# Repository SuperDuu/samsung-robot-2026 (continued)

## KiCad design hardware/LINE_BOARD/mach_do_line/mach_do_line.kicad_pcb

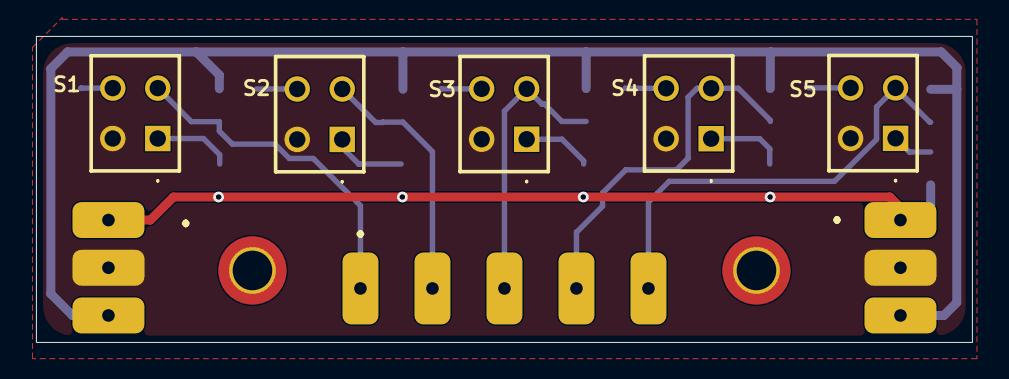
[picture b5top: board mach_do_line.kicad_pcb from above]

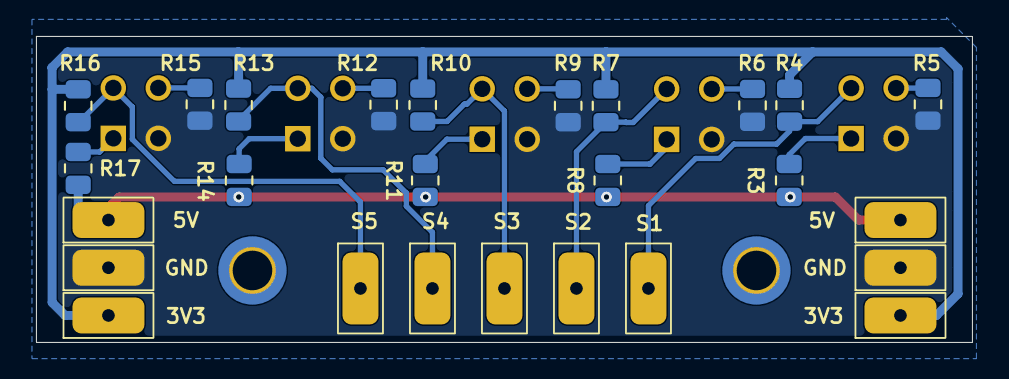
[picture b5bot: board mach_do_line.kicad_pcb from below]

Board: 2 copper layers, 52.0 x 17.0 mm, 33 parts (26 on the bottom side), 18 nets.

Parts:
3V3, 3V3#2, 5V, 5V#2: Conn_01x01_Pin; PAD-2x4mm-SMD
GND: Conn_01x01_Pin; PAD-2x4mm-SMD
GND#2: Conn_01x01_Pin; PAD-2x4mm-SMD
H1, H2: MountingHole; MountingHole_2.2mm_M2_ISO14580_Pad_TopBottom
J2, J10, J11, J12, J18: Conn_01x01_Pin; PAD-2x4mm-SMD
R3, R8, R11, R14, R17: 220R; R_0805_2012Metric
R4, R7, R10, R13, R16: 10K; R_0805_2012Metric
R5, R6, R9, R12, R15: 100R; R_0805_2012Metric
S1, S2, S3, S4, S5: RPR-220; RPR220

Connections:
+3V3: 3V3.1 (Pin_1_1), 3V3#2.1 (Pin_1_1), R4.2, R7.2, R10.2, R13.2, R16.2
+5V: 5V.1 (Pin_1_1), 5V#2.1 (Pin_1_1), R3.1, R8.1, R11.1, R14.1, R17.1
/s1: J2.1 (Pin_1_1), R4.1, S1.4 (C)
/s2: J10.1 (Pin_1_1), R7.1, S2.4 (C)
/s3: J11.1 (Pin_1_1), R10.1, S3.4 (C)
/s4: J12.1 (Pin_1_1), R13.1, S4.4 (C)
/s5: J18.1 (Pin_1_1), R16.1, S5.4 (C)
GND: GND.1 (Pin_1_1), GND#2.1 (Pin_1_1), R5.2, R6.2, R9.2, R12.2, R15.2, S1.2 (K), S2.2 (K), S3.2 (K), S4.2 (K), S5.2 (K)
unnamed: R3.2, S1.1 (A)
unnamed: R5.1, S1.3 (E)
unnamed: R8.2, S2.1 (A)
unnamed: R6.1, S2.3 (E)
unnamed: R11.2, S3.1 (A)
unnamed: R9.1, S3.3 (E)
unnamed: R14.2, S4.1 (A)
unnamed: R12.1, S4.3 (E)
unnamed: R17.2, S5.1 (A)
unnamed: R15.1, S5.3 (E)

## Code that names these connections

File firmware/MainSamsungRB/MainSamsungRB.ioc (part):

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Mcu.Name=STM32F405RGTx
Mcu.Package=LQFP64
Mcu.UserName=STM32F405RGTx
PA0-WKUP.Signal=ADCx_IN0
PA1.GPIOParameters=GPIO_Speed,PinState,GPIO_PuPd,GPIO_Label
PA1.GPIO_Label=RE_DE
PA1.GPIO_PuPd=GPIO_NOPULL
PA1.GPIO_Speed=GPIO_SPEED_FREQ_HIGH
PA1.PinState=GPIO_PIN_RESET
PA1.Signal=GPIO_Output
PA10.Mode=Asynchronous
PA10.Signal=USART1_RX
PA11.Mode=Device_Only
PA11.Signal=USB_OTG_FS_DM
PA12.Mode=Device_Only
PA12.Signal=USB_OTG_FS_DP
PA13.Mode=Serial_Wire
PA13.Signal=SYS_JTMS-SWDIO
PA14.Mode=Serial_Wire
PA14.Signal=SYS_JTCK-SWCLK
PA15.GPIOParameters=GPIO_Label
PA15.GPIO_Label=SW2
PA15.Signal=GPIO_Input
PA2.Mode=Asynchronous
PA2.Signal=USART2_TX
PA3.Mode=Asynchronous
PA3.Signal=USART2_RX
PA4.GPIOParameters=GPIO_Speed,PinState,GPIO_Label
PA4.GPIO_Label=MH_CS
PA4.GPIO_Speed=GPIO_SPEED_FREQ_HIGH
PA4.PinState=GPIO_PIN_SET
PA4.Signal=GPIO_Output
PA5.Mode=TX_Only_Simplex_Unidirect_Master
PA5.Signal=SPI1_SCK
PA7.Mode=TX_Only_Simplex_Unidirect_Master
PA7.Signal=SPI1_MOSI
PA8.Mode=I2C
PA8.Signal=I2C3_SCL
PA9.Mode=Asynchronous
PA9.Signal=USART1_TX
PB0.Signal=S_TIM3_CH3
PB1.Signal=S_TIM3_CH4
PB10.Mode=I2C
PB10.Signal=I2C2_SCL
PB11.Mode=I2C
PB11.Signal=I2C2_SDA
PB12.GPIOParameters=GPIO_Label
PB12.GPIO_Label=SW1
PB12.Signal=GPIO_Input
PB13.GPIOParameters=PinState,GPIO_Label
PB13.GPIO_Label=LS4
PB13.PinState=GPIO_PIN_RESET
PB13.Signal=GPIO_Output
PB14.Signal=S_TIM12_CH1
PB15.Signal=S_TIM12_CH2
PB2.GPIOParameters=PinState,GPIO_Label
PB2.GPIO_Label=L11
PB2.PinState=GPIO_PIN_SET
PB2.Signal=GPIO_Output
PB3.GPIOParameters=PinState,GPIO_Label
PB3.GPIO_Label=L8
PB3.PinState=GPIO_PIN_SET
PB3.Signal=GPIO_Output
PB4.GPIOParameters=PinState,GPIO_Label
PB4.GPIO_Label=L7
PB4.PinState=GPIO_PIN_SET
PB4.Signal=GPIO_Output
PB5.GPIOParameters=PinState,GPIO_Label
PB5.GPIO_Label=L6
PB5.PinState=GPIO_PIN_SET
PB5.Signal=GPIO_Output
PB6.GPIOParameters=PinState,GPIO_Label
PB6.GPIO_Label=L5
PB6.PinState=GPIO_PIN_SET
PB6.Signal=GPIO_Output
PB7.GPIOParameters=PinState,GPIO_Label
PB7.GPIO_Label=L4
PB7.PinState=GPIO_PIN_SET
PB7.Signal=GPIO_Output
PB8.Signal=S_TIM4_CH3
PB9.Signal=S_TIM4_CH4
PC0.GPIOParameters=GPIO_Speed,PinState,GPIO_Label
PC0.GPIO_Label=s3
PC0.GPIO_Speed=GPIO_SPEED_FREQ_VERY_HIGH
PC0.PinState=GPIO_PIN_RESET
PC0.Signal=GPIO_Output
PC1.GPIOParameters=GPIO_Speed,PinState,GPIO_Label
PC1.GPIO_Label=s2
PC1.GPIO_Speed=GPIO_SPEED_FREQ_VERY_HIGH
PC1.PinState=GPIO_PIN_RESET
PC1.Signal=GPIO_Output
PC10.Mode=Asynchronous
PC10.Signal=UART4_TX
PC11.Mode=Asynchronous
PC11.Signal=UART4_RX
PC12.GPIOParameters=PinState,GPIO_Label
PC12.GPIO_Label=L10
PC12.PinState=GPIO_PIN_SET
PC12.Signal=GPIO_Output
PC13-ANTI_TAMP.GPIOParameters=PinState,GPIO_Label
PC13-ANTI_TAMP.GPIO_Label=L3
PC13-ANTI_TAMP.PinState=GPIO_PIN_SET
PC13-ANTI_TAMP.Signal=GPIO_Output
PC14-OSC32_IN.GPIOParameters=PinState,GPIO_Label
PC14-OSC32_IN.GPIO_Label=L2
PC14-OSC32_IN.PinState=GPIO_PIN_SET
PC14-OSC32_IN.Signal=GPIO_Output
PC15-OSC32_OUT.GPIOParameters=PinState,GPIO_Label
PC15-OSC32_OUT.GPIO_Label=L1
PC15-OSC32_OUT.PinState=GPIO_PIN_SET
PC15-OSC32_OUT.Signal=GPIO_Output
PC2.GPIOParameters=GPIO_Speed,PinState,GPIO_Label
PC2.GPIO_Label=s1
PC2.GPIO_Speed=GPIO_SPEED_FREQ_VERY_HIGH
PC2.PinState=GPIO_PIN_RESET
PC2.Signal=GPIO_Output
PC3.GPIOParameters=GPIO_Speed,PinState,GPIO_Label
PC3.GPIO_Label=s0
PC3.GPIO_Speed=GPIO_SPEED_FREQ_VERY_HIGH
PC3.PinState=GPIO_PIN_RESET
PC3.Signal=GPIO_Output
PC4.GPIOParameters=GPIO_Speed,PinState,GPIO_Label
PC4.GPIO_Label=MH_RST
PC4.GPIO_Speed=GPIO_SPEED_FREQ_LOW
PC4.PinState=GPIO_PIN_SET
PC4.Signal=GPIO_Output
PC5.GPIOParameters=GPIO_Speed,PinState,GPIO_Label
PC5.GPIO_Label=MH_DC
PC5.GPIO_Speed=GPIO_SPEED_FREQ_HIGH
PC5.PinState=GPIO_PIN_RESET
PC5.Signal=GPIO_Output
PC6.GPIOParameters=PinState,GPIO_Label
PC6.GPIO_Label=LS3
PC6.PinState=GPIO_PIN_RESET
PC6.Signal=GPIO_Output
PC7.GPIOParameters=PinState,GPIO_Label
PC7.GPIO_Label=LS2
PC7.PinState=GPIO_PIN_RESET
PC7.Signal=GPIO_Output
PC8.GPIOParameters=PinState,GPIO_Label
PC8.GPIO_Label=LS1
PC8.PinState=GPIO_PIN_RESET
PC8.Signal=GPIO_Output
PC9.Mode=I2C
PC9.Signal=I2C3_SDA
PD2.GPIOParameters=PinState,GPIO_Label
PD2.GPIO_Label=L9
PD2.PinState=GPIO_PIN_SET
PD2.Signal=GPIO_Output
PH0-OSC_IN.Mode=HSE-External-Oscillator
PH0-OSC_IN.Signal=RCC_OSC_IN
PH1-OSC_OUT.Mode=HSE-External-Oscillator
PH1-OSC_OUT.Signal=RCC_OSC_OUT
RCC.HSE_VALUE=8000000
RCC.SYSCLKFreq_VALUE=168000000
RCC.SYSCLKSource=RCC_SYSCLKSOURCE_PLLCLK
board=custom

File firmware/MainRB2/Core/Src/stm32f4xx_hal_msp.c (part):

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
    __HAL_RCC_GPIOA_CLK_ENABLE();
    /**ADC1 GPIO Configuration
    PA0-WKUP     ------> ADC1_IN0
    */
    GPIO_InitStruct.Pin = GPIO_PIN_0;
    GPIO_InitStruct.Mode = GPIO_MODE_ANALOG;
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    __HAL_RCC_ADC1_CLK_DISABLE();

    /**ADC1 GPIO Configuration
    PA0-WKUP     ------> ADC1_IN0
    */
    HAL_GPIO_DeInit(GPIOA, GPIO_PIN_0);

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
    __HAL_RCC_GPIOB_CLK_ENABLE();
    /**I2C2 GPIO Configuration
    PB10     ------> I2C2_SCL
    PB11     ------> I2C2_SDA
    */
    GPIO_InitStruct.Pin = GPIO_PIN_10|GPIO_PIN_11;
    GPIO_InitStruct.Mode = GPIO_MODE_AF_OD;
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    __HAL_RCC_GPIOC_CLK_ENABLE();
    __HAL_RCC_GPIOA_CLK_ENABLE();
    /**I2C3 GPIO Configuration
    PC9     ------> I2C3_SDA
    PA8     ------> I2C3_SCL
    */
    GPIO_InitStruct.Pin = GPIO_PIN_9;
    GPIO_InitStruct.Mode = GPIO_MODE_AF_OD;
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    __HAL_RCC_I2C2_CLK_DISABLE();

    /**I2C2 GPIO Configuration
    PB10     ------> I2C2_SCL
    PB11     ------> I2C2_SDA
    */
    HAL_GPIO_DeInit(GPIOB, GPIO_PIN_10);

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    __HAL_RCC_I2C3_CLK_DISABLE();

    /**I2C3 GPIO Configuration
    PC9     ------> I2C3_SDA
    PA8     ------> I2C3_SCL
    */
    HAL_GPIO_DeInit(GPIOC, GPIO_PIN_9);

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
    __HAL_RCC_GPIOA_CLK_ENABLE();
    /**SPI1 GPIO Configuration
    PA5     ------> SPI1_SCK
    PA7     ------> SPI1_MOSI
    */
    GPIO_InitStruct.Pin = GPIO_PIN_5|GPIO_PIN_7;
    GPIO_InitStruct.Mode = GPIO_MODE_AF_PP;
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    __HAL_RCC_SPI1_CLK_DISABLE();

    /**SPI1 GPIO Configuration
    PA5     ------> SPI1_SCK
    PA7     ------> SPI1_MOSI
    */
    HAL_GPIO_DeInit(GPIOA, GPIO_PIN_5|GPIO_PIN_7);

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    /* USER CODE END TIM4_MspPostInit 0 */
    __HAL_RCC_GPIOB_CLK_ENABLE();
    /**TIM4 GPIO Configuration
    PB8     ------> TIM4_CH3
    */
    GPIO_InitStruct.Pin = GPIO_PIN_8;
    GPIO_InitStruct.Mode = GPIO_MODE_AF_PP;
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
    __HAL_RCC_GPIOB_CLK_ENABLE();
    /**TIM12 GPIO Configuration
    PB15     ------> TIM12_CH2
    */
    GPIO_InitStruct.Pin = GPIO_PIN_15;
    GPIO_InitStruct.Mode = GPIO_MODE_AF_PP;
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
    __HAL_RCC_GPIOC_CLK_ENABLE();
    /**UART4 GPIO Configuration
    PC10     ------> UART4_TX
    PC11     ------> UART4_RX
    */
    GPIO_InitStruct.Pin = GPIO_PIN_10|GPIO_PIN_11;
    GPIO_InitStruct.Mode = GPIO_MODE_AF_PP;
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
    __HAL_RCC_GPIOA_CLK_ENABLE();
    /**USART1 GPIO Configuration
    PA9     ------> USART1_TX
    PA10     ------> USART1_RX
    */
    GPIO_InitStruct.Pin = GPIO_PIN_9|GPIO_PIN_10;
    GPIO_InitStruct.Mode = GPIO_MODE_AF_PP;
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
    __HAL_RCC_GPIOA_CLK_ENABLE();
    /**USART2 GPIO Configuration
    PA2     ------> USART2_TX
    PA3     ------> USART2_RX
    */
    GPIO_InitStruct.Pin = GPIO_PIN_2|GPIO_PIN_3;
    GPIO_InitStruct.Mode = GPIO_MODE_AF_PP;
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    __HAL_RCC_UART4_CLK_DISABLE();

    /**UART4 GPIO Configuration
    PC10     ------> UART4_TX
    PC11     ------> UART4_RX
    */
    HAL_GPIO_DeInit(GPIOC, GPIO_PIN_10|GPIO_PIN_11);

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    __HAL_RCC_USART1_CLK_DISABLE();

    /**USART1 GPIO Configuration
    PA9     ------> USART1_TX
    PA10     ------> USART1_RX
    */
    HAL_GPIO_DeInit(GPIOA, GPIO_PIN_9|GPIO_PIN_10);

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    __HAL_RCC_USART2_CLK_DISABLE();

    /**USART2 GPIO Configuration
    PA2     ------> USART2_TX
    PA3     ------> USART2_RX
    */
    HAL_GPIO_DeInit(GPIOA, GPIO_PIN_2|GPIO_PIN_3);

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
    __HAL_RCC_GPIOA_CLK_ENABLE();
    /**USB_OTG_FS GPIO Configuration
    PA11     ------> USB_OTG_FS_DM
    PA12     ------> USB_OTG_FS_DP
    */
    GPIO_InitStruct.Pin = GPIO_PIN_11|GPIO_PIN_12;
    GPIO_InitStruct.Mode = GPIO_MODE_AF_PP;
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    __HAL_RCC_USB_OTG_FS_CLK_DISABLE();

    /**USB_OTG_FS GPIO Configuration
    PA11     ------> USB_OTG_FS_DM
    PA12     ------> USB_OTG_FS_DP
    */
    HAL_GPIO_DeInit(GPIOA, GPIO_PIN_11|GPIO_PIN_12);

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
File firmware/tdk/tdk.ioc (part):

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Mcu.Name=STM32G030F6Px
Mcu.Package=TSSOP20
Mcu.UserName=STM32G030F6Px
PA1.GPIOParameters=GPIO_Speed,PinState,GPIO_PuPd,GPIO_Label
PA1.GPIO_Label=CLK_PS2
PA1.GPIO_PuPd=GPIO_NOPULL
PA1.GPIO_Speed=GPIO_SPEED_FREQ_HIGH
PA1.PinState=GPIO_PIN_SET
PA1.Signal=GPIO_Output
PA11\ [PA9].GPIOParameters=PinState,GPIO_Label
PA11\ [PA9].GPIO_Label=BUZZER
PA11\ [PA9].PinState=GPIO_PIN_RESET
PA11\ [PA9].Signal=GPIO_Output
PA12\ [PA10].GPIOParameters=PinState,GPIO_Label
PA12\ [PA10].GPIO_Label=LED_1
PA12\ [PA10].PinState=GPIO_PIN_RESET
PA12\ [PA10].Signal=GPIO_Output
PA13.Mode=Serial_Wire
PA13.Signal=SYS_SWDIO
PA14-BOOT0.Mode=Serial_Wire
PA14-BOOT0.Signal=SYS_SWCLK
PA14-BOOT0__PA15.StandardMode=true
PA2.Mode=Asynchronous
PA2.Signal=USART2_TX
PA3.Mode=Asynchronous
PA3.Signal=USART2_RX
PA4.GPIOParameters=GPIO_Speed,PinState,GPIO_PuPd,GPIO_Label
PA4.GPIO_Label=CS_PS2
PA4.GPIO_PuPd=GPIO_NOPULL
PA4.GPIO_Speed=GPIO_SPEED_FREQ_HIGH
PA4.PinState=GPIO_PIN_SET
PA4.Signal=GPIO_Output
PA6.GPIOParameters=PinState,GPIO_Label
PA6.GPIO_Label=LED_3
PA6.PinState=GPIO_PIN_RESET
PA6.Signal=GPIO_Output
PA8.GPIOParameters=GPIO_PuPd,GPIO_Label
PA8.GPIO_Label=SW
PA8.GPIO_PuPd=GPIO_NOPULL
PA8.Signal=GPIO_Input
PB0__PB1__PB2__PA8.StandardMode=true
PB3.GPIOParameters=GPIO_PuPd,GPIO_Label
PB3.GPIO_Label=BUTTON
PB3.GPIO_PuPd=GPIO_NOPULL
PB3.Signal=GPIO_Input
PB3__PB4__PB5__PB6.StandardMode=true
PB7.GPIOParameters=GPIO_Speed,PinState,GPIO_PuPd,GPIO_Label
PB7.GPIO_Label=DO_PS2
PB7.GPIO_PuPd=GPIO_NOPULL
PB7.GPIO_Speed=GPIO_SPEED_FREQ_HIGH
PB7.PinState=GPIO_PIN_SET
PB7.Signal=GPIO_Output
PB7__PB8.StandardMode=true
PB9.GPIOParameters=PinState,GPIO_Label
PB9.GPIO_Label=LED_2
PB9.PinState=GPIO_PIN_RESET
PB9.Signal=GPIO_Output
PC14-OSC32_IN\ (PC14)__PB9.StandardMode=true
PC15-OSC32_OUT\ (PC15).GPIOParameters=GPIO_PuPd,GPIO_Label
PC15-OSC32_OUT\ (PC15).GPIO_Label=DI_PS2
PC15-OSC32_OUT\ (PC15).GPIO_PuPd=GPIO_PULLUP
PC15-OSC32_OUT\ (PC15).Signal=GPIO_Input
RCC.HSE_VALUE=8000000
RCC.SYSCLKFreq_VALUE=64000000
RCC.SYSCLKSource=RCC_SYSCLKSOURCE_PLLCLK
board=custom

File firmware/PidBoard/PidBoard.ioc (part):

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Mcu.Name=STM32G030F6Px
Mcu.Package=TSSOP20
Mcu.UserName=STM32G030F6Px
PA1.GPIOParameters=GPIO_Speed,PinState,GPIO_PuPd,GPIO_Label
PA1.GPIO_Label=RE_DE
PA1.GPIO_PuPd=GPIO_NOPULL
PA1.GPIO_Speed=GPIO_SPEED_FREQ_HIGH
PA1.PinState=GPIO_PIN_RESET
PA1.Signal=GPIO_Output
PA13.Mode=Serial_Wire
PA13.Signal=SYS_SWDIO
PA14-BOOT0.Mode=Serial_Wire
PA14-BOOT0.Signal=SYS_SWCLK
PA14-BOOT0__PA15.StandardMode=true
PA2.Mode=Asynchronous
PA2.Signal=USART2_TX
PA3.Mode=Asynchronous
PA3.Signal=USART2_RX
PA4.GPIOParameters=GPIO_Speed,PinState,GPIO_PuPd,GPIO_Label
PA4.GPIO_Label=S2
PA4.GPIO_PuPd=GPIO_NOPULL
PA4.GPIO_Speed=GPIO_SPEED_FREQ_LOW
PA4.PinState=GPIO_PIN_RESET
PA4.Signal=GPIO_Output
PA6.GPIOParameters=GPIO_PuPd,GPIO_Label
PA6.GPIO_Label=ENC_A
PA6.GPIO_PuPd=GPIO_PULLUP
PA6.Signal=S_TIM3_CH1
PA7.GPIOParameters=GPIO_PuPd,GPIO_Label
PA7.GPIO_Label=ENC_B
PA7.GPIO_PuPd=GPIO_PULLUP
PA7.Signal=S_TIM3_CH2
PA8.Signal=S_TIM1_CH1
PB0__PB1__PB2__PA8.StandardMode=true
PB3.Signal=S_TIM1_CH2
PB3__PB4__PB5__PB6.StandardMode=true
PB7.GPIOParameters=GPIO_Speed,PinState,GPIO_PuPd,GPIO_Label
PB7.GPIO_Label=S
PB7.GPIO_PuPd=GPIO_NOPULL
PB7.GPIO_Speed=GPIO_SPEED_FREQ_LOW
PB7.PinState=GPIO_PIN_RESET
PB7.Signal=GPIO_Output
PB7__PB8.StandardMode=true
PC14-OSC32_IN\ (PC14).GPIOParameters=GPIO_Speed,PinState,GPIO_PuPd,GPIO_Label
PC14-OSC32_IN\ (PC14).GPIO_Label=LED2
PC14-OSC32_IN\ (PC14).GPIO_PuPd=GPIO_NOPULL
PC14-OSC32_IN\ (PC14).GPIO_Speed=GPIO_SPEED_FREQ_LOW
PC14-OSC32_IN\ (PC14).PinState=GPIO_PIN_SET
PC14-OSC32_IN\ (PC14).Signal=GPIO_Output
PC14-OSC32_IN\ (PC14)__PB9.StandardMode=true
PC15-OSC32_OUT\ (PC15).GPIOParameters=GPIO_Speed,PinState,GPIO_PuPd,GPIO_Label
PC15-OSC32_OUT\ (PC15).GPIO_Label=LED1
PC15-OSC32_OUT\ (PC15).GPIO_PuPd=GPIO_NOPULL
PC15-OSC32_OUT\ (PC15).GPIO_Speed=GPIO_SPEED_FREQ_LOW
PC15-OSC32_OUT\ (PC15).PinState=GPIO_PIN_SET
PC15-OSC32_OUT\ (PC15).Signal=GPIO_Output
RCC.HSE_VALUE=8000000
RCC.SYSCLKFreq_VALUE=64000000
RCC.SYSCLKSource=RCC_SYSCLKSOURCE_PLLCLK
board=custom

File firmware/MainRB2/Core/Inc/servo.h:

/**
  ******************************************************************************
  * @file    servo.h
  * @brief   2-mode Servo driver (0-270 deg positional & 360 deg continuous speed)
  *          for the PWM outputs on MainRB2 (TIM3 CH3/4, TIM12 CH2, TIM4 CH3/4).
  *          Requires 50 Hz timer base: PSC = 83, ARR = 19999 -> 1 tick = 1 us.
  ******************************************************************************
  */

#ifndef INC_SERVO_H_
#define INC_SERVO_H_

#ifdef __cplusplus
extern "C" {
#endif

#ifdef UNIT_TEST_HOST
#include "mock_hal.h"
#else
#include "main.h"
#endif

#include <stdbool.h>
#include <stdint.h>

#define SERVO_PWM_MIN_US               500U
#define SERVO_PWM_NEUTRAL_US           1500U
#define SERVO_PWM_MAX_US               2500U
#define SERVO_180_MAX_DEG              180.0f
#define SERVO_270_MAX_DEG              270.0f
#define SERVO_CLAMP_DEFAULT_OPEN_DEG   15.0f
#define SERVO_CLAMP_DEFAULT_CLOSE_DEG  0.0f
#define SERVO_360_DEFAULT_HALF_SPAN_US 500U   /* 1000..2000 us continuous range (pass 1000 for 500..2500 us) */
#define SERVO_DEFAULT_DEADBAND_PCT     2.0f

typedef enum
{
  SERVO_CH_1 = 0U, /* PB0  - TIM3_CH3  (J2)  */
  SERVO_CH_2 = 1U, /* Reserved: PB1 (J34) is BAUMER_INPUT */
  SERVO_CH_3 = 2U, /* Unused: PB14 (J35) */
  SERVO_CH_4 = 3U, /* PB15 - TIM12_CH2 (J36) */
  SERVO_CH_5 = 4U, /* PB8  - TIM4_CH3  (J37) */
  SERVO_CH_6 = 5U, /* PB9  - TIM4_CH4  (J38) */
  SERVO_NUM_CHANNELS = 6U
} Servo_Channel_t;

typedef enum
{
  SERVO_MODE_UNCONFIGURED   = 0U,
  SERVO_MODE_ANGLE_270      = 1U,
  SERVO_MODE_CONTINUOUS_360 = 2U,
  SERVO_MODE_ANGLE_180      = 3U
} Servo_Mode_t;

typedef struct
{
  Servo_Mode_t mode;
  uint16_t     min_us;
  uint16_t     neutral_us;
  uint16_t     max_us;
  float        deadband_pct;
  bool         inverted;
  bool         started;
  uint16_t     current_us;
  float        last_cmd;
} Servo_ChannelState_t;

HAL_StatusTypeDef Servo_Init(TIM_HandleTypeDef *htim3,
                             TIM_HandleTypeDef *htim4,
                             TIM_HandleTypeDef *htim12);

HAL_StatusTypeDef Servo_Config270(Servo_Channel_t ch,
                                  uint16_t min_us,
                                  uint16_t max_us,
                                  bool inverted);

HAL_StatusTypeDef Servo_Config180(Servo_Channel_t ch,
                                  uint16_t min_us,
                                  uint16_t max_us,
                                  bool inverted);

HAL_StatusTypeDef Servo_Config360(Servo_Channel_t ch,
                                  uint16_t neutral_us,
                                  uint16_t half_span_us,
                                  float deadband_pct,
                                  bool inverted);

/* Mode 1: Positional 0.0 .. 270.0 degrees (linearly mapped to min_us..max_us) */
HAL_StatusTypeDef Servo_SetAngle270(Servo_Channel_t ch, float angle_deg);

/* Mode 3: Positional 0.0 .. 180.0 degrees (linearly mapped to min_us..max_us) */
HAL_StatusTypeDef Servo_SetAngle180(Servo_Channel_t ch, float angle_deg);

/* Mode 2: Continuous 360 rotation (-100.0% CCW .. 0.0% stop .. +100.0% CW) */
HAL_StatusTypeDef Servo_SetSpeed360(Servo_Channel_t ch, float speed_pct);

/* Convenience helper for 360 mode: dir > 0 CW, dir < 0 CCW, dir == 0 stop */
HAL_StatusTypeDef Servo_SetDirection360(Servo_Channel_t ch, int8_t dir, float speed_abs_pct);

/* Stops 360 continuous servo at neutral_us, or cuts PWM pulse (0 us) on 270 servo */
HAL_StatusTypeDef Servo_Stop(Servo_Channel_t ch);
void Servo_StopAll360(void);

HAL_StatusTypeDef Servo_WriteRawUs(Servo_Channel_t ch, uint16_t pulse_us);
bool Servo_GetState(Servo_Channel_t ch, Servo_ChannelState_t *out_state);

#ifdef __cplusplus
}
#endif

#endif /* INC_SERVO_H_ */

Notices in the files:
firmware/MainRB2/Core/Src/stm32f4xx_hal_msp.c:
Copyright (c) 2026 STMicroelectronics.
All rights reserved.
This software is licensed under terms that can be found in the LICENSE file
